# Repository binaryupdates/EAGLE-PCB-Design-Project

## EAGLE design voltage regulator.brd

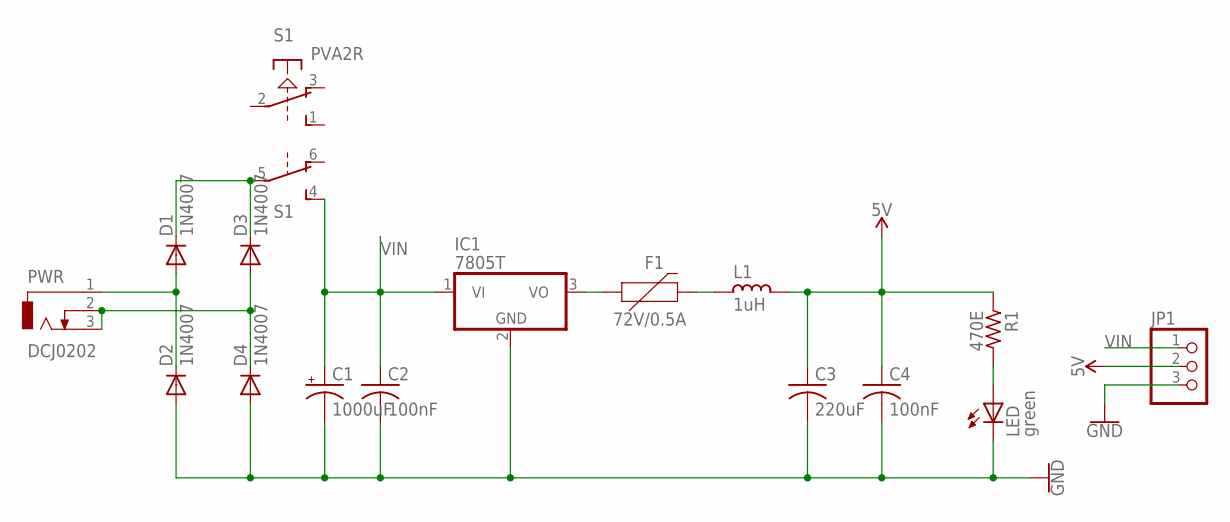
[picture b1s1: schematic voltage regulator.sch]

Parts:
C1: 1000uF; E5-13
C2, C4: 100nF; C0805
C3: 220uF; C0805
D1, D2, D3, D4: 1N4007; DO41-10
F1: 72V/0.5A; PTH
IC1: 7805T; TO220H
JP1: PINHD-1X3; 1X03
L1: 1uH; L0805
LED: green; CHIP-LED0805
PWR: DCJ0202
R1: 470E; R0805
S1: PVA2R

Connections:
5V: C3.1, C4.1, JP1.2, L1.1, R1.1
GND: C1.-, C2.2, C3.2, C4.2, D2.A, D4.A, IC1.2 (GND), JP1.3, LED.C
unnamed: D1.C, D3.C, S1.5
unnamed: D1.A, D2.C, PWR.1
unnamed: D3.A, D4.C, PWR.2, PWR.3
unnamed: F1.P$1 (1), IC1.3 (VO)
unnamed: F1.P$2 (2), L1.2
unnamed: LED.A, R1.2
VIN: C1.+, C2.1, IC1.1 (VI), JP1.1, S1.4 (S)

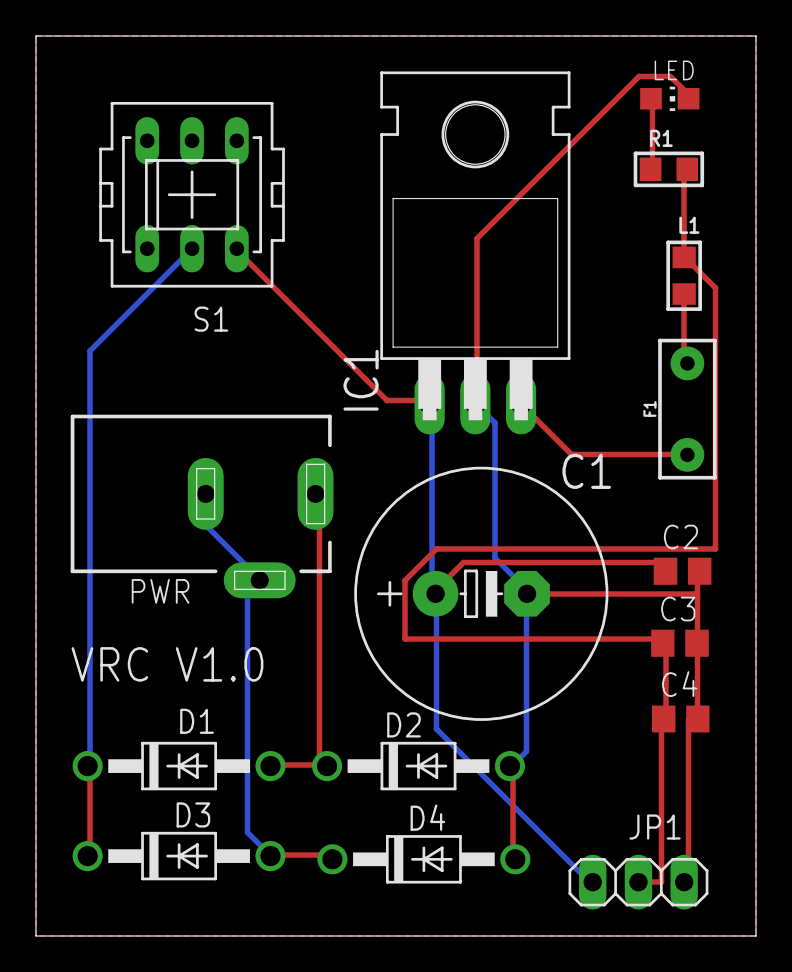
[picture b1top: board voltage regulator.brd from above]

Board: 2 copper layers, 40.0 x 50.0 mm, 16 parts (0 on the bottom side), 9 nets.

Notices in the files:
parts and their libraries:
SparkFun-Fuses: Licensing: Creative Commons ShareAlike 4.0 International - https://creativecommons.org/licenses/by-sa/4.0
rc-master-smd: Copyright (C) 2007, Bob Starr
